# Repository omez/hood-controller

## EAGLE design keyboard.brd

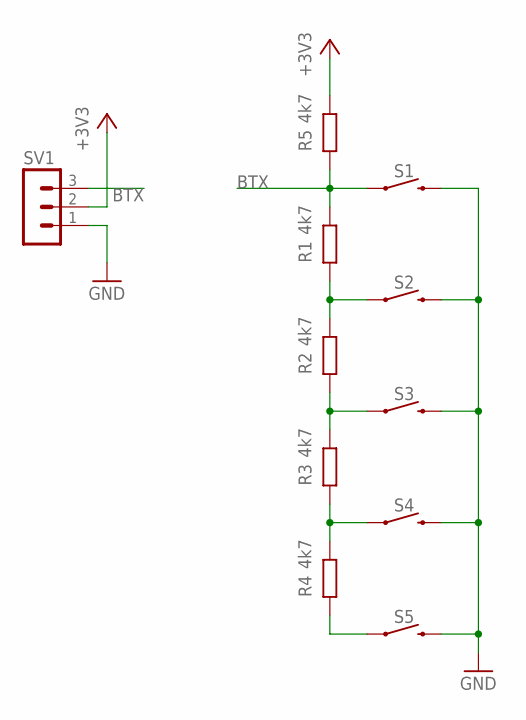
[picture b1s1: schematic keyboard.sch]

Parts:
R1, R2, R3, R4, R5: 4k7; R1206
S1, S2, S3, S4, S5: MOMENTARY-SWITCH-SPST-PTH-6.0MM; TACTILE_SWITCH_PTH_6.0MM
SV1: MA03-1

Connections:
+3V3: R5.2, SV1.2
BTX: R1.2, R5.1, S1.1, SV1.3
GND: S1.3 (2), S2.3 (2), S3.3 (2), S4.3 (2), S5.3 (2), SV1.1
unnamed: R3.1, R4.2, S4.1
unnamed: R4.1, S5.1
unnamed: R2.1, R3.2, S3.1
unnamed: R1.1, R2.2, S2.1

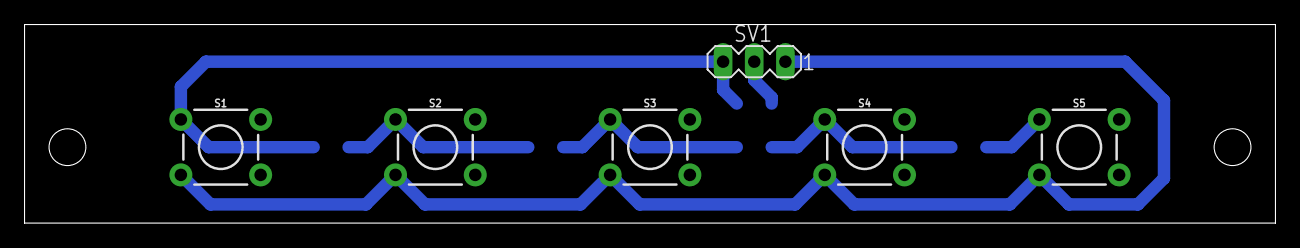
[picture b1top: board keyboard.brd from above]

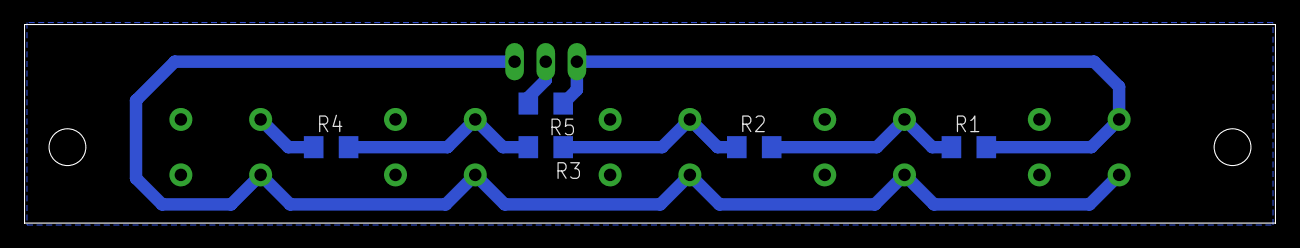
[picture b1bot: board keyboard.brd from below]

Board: 2 copper layers, 102.0 x 16.2 mm, 11 parts (5 on the bottom side), 7 nets.

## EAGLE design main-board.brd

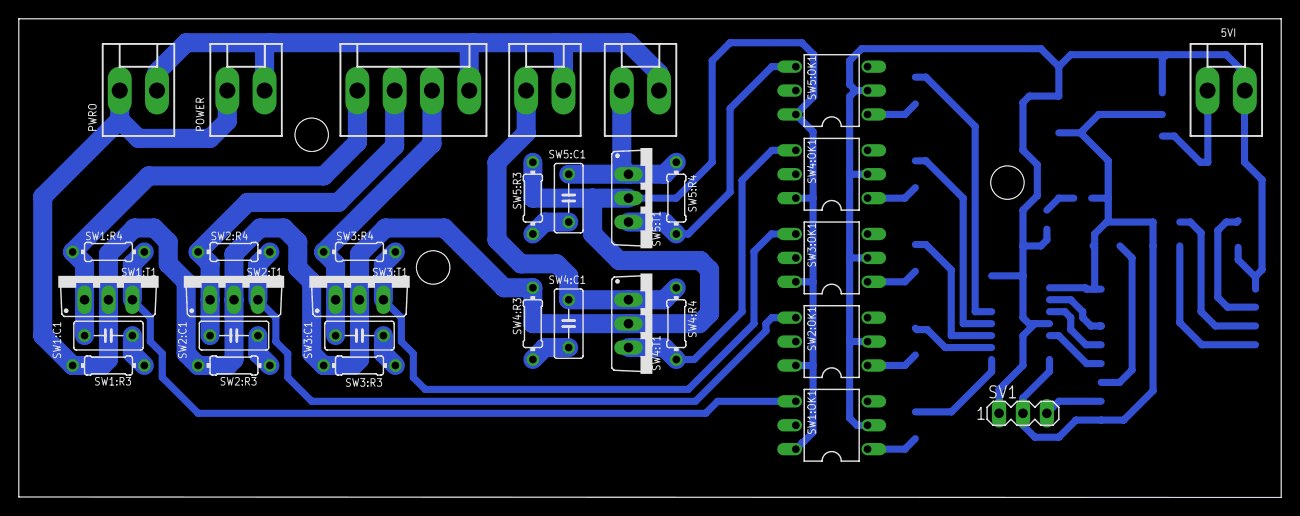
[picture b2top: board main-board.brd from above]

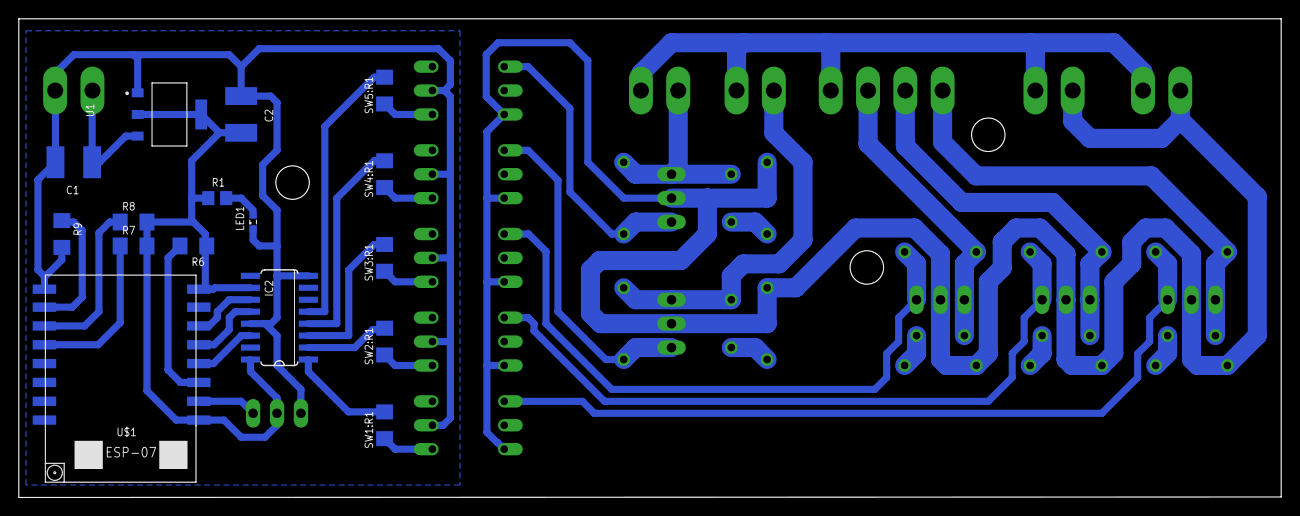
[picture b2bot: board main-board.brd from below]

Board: 2 copper layers, 134.1 x 50.9 mm, 48 parts (16 on the bottom side), 39 nets.

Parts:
5VI: KK-156-2
C1, C2: C4532
IC2: 74HC595D; SO16
LAMP1, LAMP2: KK-156-2
LED1: SML0603
MOTOR: KK-156-4
POWER: KK-156-2
PWRO: KK-156-2
R1: 210; R0805
R6, R7, R8, R9: 4k7; R1206
SV1: MA03-1
SW1:C1, SW2:C1, SW3:C1, SW4:C1, SW5:C1: C050-030X075
SW1:OK1, SW2:OK1, SW3:OK1, SW4:OK1, SW5:OK1: MOC3033M; DIL06
SW1:R1, SW2:R1, SW3:R1, SW4:R1, SW5:R1: 100; R1206
SW1:R3, SW2:R3, SW3:R3, SW4:R3, SW5:R3: 39; 0204/7
SW1:R4, SW2:R4, SW3:R4, SW4:R4, SW5:R4: 360; 0204/7
SW1:T1, SW2:T1, SW3:T1, SW4:T1, SW5:T1: BT138-V; TO220BV
U1: LD1117S33TR; SOT-223
U$1: ESP07-16PIN

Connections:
+3V3: C2.1, IC2.10, IC2.16, R1.1, R6.1, R7.2, R8.2, SV1.2, U1.2, U1.4, U$1.REST, U$1.VCC
+5V: 5VI.1, C1.1, U1.3
AC+: POWER.1, PWRO.1, SW1:OK1.6, SW1:R3.2, SW1:T1.T2, SW2:OK1.6, SW2:R3.2, SW2:T1.T2, SW3:OK1.6, SW3:R3.2, SW3:T1.T2, SW4:OK1.6, SW4:R3.2, SW4:T1.T2, SW5:OK1.6, SW5:R3.2, SW5:T1.T2
AC-: LAMP1.2, LAMP2.2, MOTOR.4, POWER.2, PWRO.2
BTX: SV1.3, U$1.ADC
CDT: IC2.14, U$1.GPIO16
CLT: IC2.12, U$1.GPIO14
CSCK: IC2.11, U$1.GPIO12
GND: 5VI.2, C1.2, C2.2, IC2.8, IC2.13, LED1.C, R9.2, SV1.1, SW1:OK1.2, SW2:OK1.2, SW3:OK1.2, SW4:OK1.2, SW5:OK1.2, U1.1, U$1.GND
LAMP1: LAMP1.1, SW5:C1.2, SW5:R4.1, SW5:T1.T1
LAMP2: LAMP2.1, SW4:C1.2, SW4:R4.1, SW4:T1.T1
M1: MOTOR.1, SW1:C1.2, SW1:R4.1, SW1:T1.T1
M2: MOTOR.2, SW2:C1.2, SW2:R4.1, SW2:T1.T1
M3: MOTOR.3, SW3:C1.2, SW3:R4.1, SW3:T1.T1
unnamed: IC2.2, SW2:R1.1
unnamed: LED1.A, R1.2
unnamed: IC2.4, SW4:R1.1
unnamed: IC2.1, SW1:R1.1
unnamed: IC2.3, SW3:R1.1
unnamed: IC2.5, SW5:R1.1
unnamed: R6.2, U$1.CH_PD
unnamed: R7.1, U$1.GPIO0
unnamed: R8.1, U$1.GPIO2
unnamed: R9.1, U$1.GPIO15
SW1:ACS: SW1:OK1.4, SW1:R4.2, SW1:T1.G
SW1:N$1: SW1:OK1.1, SW1:R1.2
SW1:N$8: SW1:C1.1, SW1:R3.1
SW2:ACS: SW2:OK1.4, SW2:R4.2, SW2:T1.G
SW2:N$1: SW2:OK1.1, SW2:R1.2
SW2:N$8: SW2:C1.1, SW2:R3.1
SW3:ACS: SW3:OK1.4, SW3:R4.2, SW3:T1.G
SW3:N$1: SW3:OK1.1, SW3:R1.2
SW3:N$8: SW3:C1.1, SW3:R3.1
SW4:ACS: SW4:OK1.4, SW4:R4.2, SW4:T1.G
SW4:N$1: SW4:OK1.1, SW4:R1.2
SW4:N$8: SW4:C1.1, SW4:R3.1
SW5:ACS: SW5:OK1.4, SW5:R4.2, SW5:T1.G
SW5:N$1: SW5:OK1.1, SW5:R1.2
SW5:N$8: SW5:C1.1, SW5:R3.1

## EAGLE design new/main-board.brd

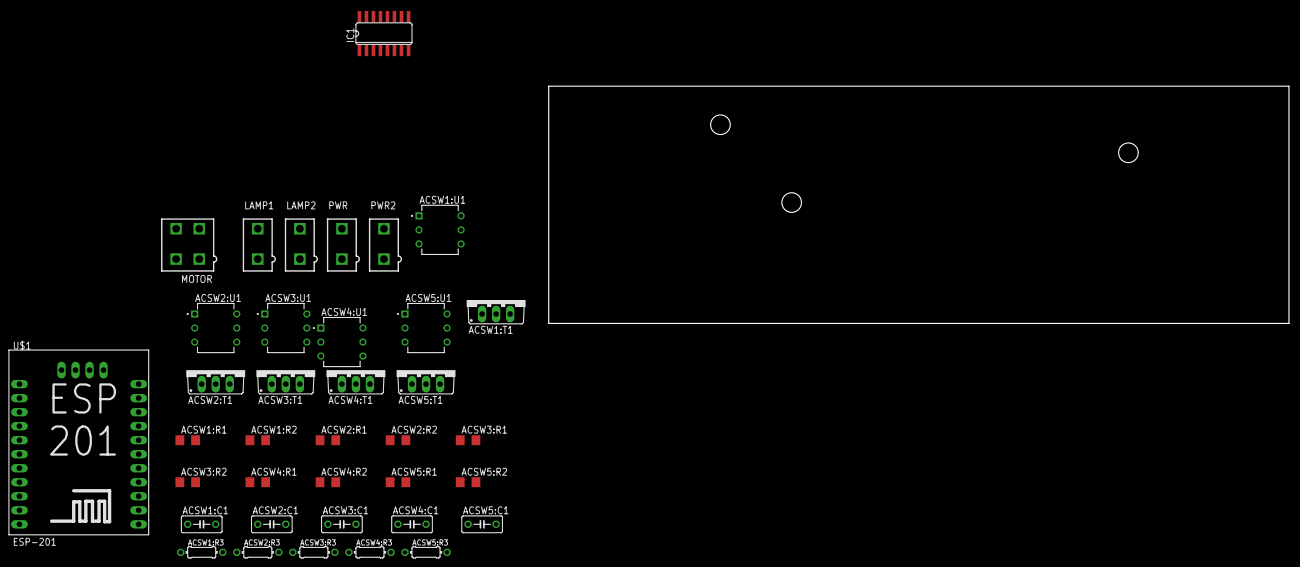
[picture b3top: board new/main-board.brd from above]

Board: 2 copper layers, 134.1 x 43.0 mm, 37 parts (0 on the bottom side), 38 nets, no tracks yet.

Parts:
ACSW1:C1, ACSW2:C1, ACSW3:C1, ACSW4:C1, ACSW5:C1: C050-030X075
ACSW1:R1, ACSW2:R1, ACSW3:R1, ACSW4:R1, ACSW5:R1: 100; R1206
ACSW1:R2, ACSW2:R2, ACSW3:R2, ACSW4:R2, ACSW5:R2: 360; R1206
ACSW1:R3, ACSW2:R3, ACSW3:R3, ACSW4:R3, ACSW5:R3: 0204/7
ACSW1:T1, ACSW2:T1, ACSW3:T1, ACSW4:T1, ACSW5:T1: BT138-V; TO220BV
ACSW1:U1, ACSW2:U1, ACSW3:U1, ACSW4:U1, ACSW5:U1: MOC3012M
IC1: 74LS595D; SO16
LAMP1, LAMP2: 5566-2
MOTOR: 5566-4
PWR, PWR2: 5566-2
U$1: ESP-201

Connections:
ACSW1:AC+: ACSW1:R3.2, ACSW1:T1.T2, ACSW1:U1.6
ACSW1:AC-: ACSW1:C1.2, ACSW1:T1.T1
ACSW1:N$1: ACSW1:R1.2, ACSW1:U1.1
ACSW1:N$2: ACSW1:R2.1, ACSW1:U1.4
ACSW1:N$5: ACSW1:R2.2, ACSW1:T1.G
ACSW1:N$8: ACSW1:C1.1, ACSW1:R3.1
ACSW2:AC+: ACSW2:R3.2, ACSW2:T1.T2, ACSW2:U1.6
ACSW2:AC-: ACSW2:C1.2, ACSW2:T1.T1
ACSW2:N$1: ACSW2:R1.2, ACSW2:U1.1
ACSW2:N$2: ACSW2:R2.1, ACSW2:U1.4
ACSW2:N$5: ACSW2:R2.2, ACSW2:T1.G
ACSW2:N$8: ACSW2:C1.1, ACSW2:R3.1
ACSW3:AC+: ACSW3:R3.2, ACSW3:T1.T2, ACSW3:U1.6
ACSW3:AC-: ACSW3:C1.2, ACSW3:T1.T1
ACSW3:N$1: ACSW3:R1.2, ACSW3:U1.1
ACSW3:N$2: ACSW3:R2.1, ACSW3:U1.4
ACSW3:N$5: ACSW3:R2.2, ACSW3:T1.G
ACSW3:N$8: ACSW3:C1.1, ACSW3:R3.1
ACSW4:AC+: ACSW4:R3.2, ACSW4:T1.T2, ACSW4:U1.6
ACSW4:AC-: ACSW4:C1.2, ACSW4:T1.T1
ACSW4:N$1: ACSW4:R1.2, ACSW4:U1.1
ACSW4:N$2: ACSW4:R2.1, ACSW4:U1.4
ACSW4:N$5: ACSW4:R2.2, ACSW4:T1.G
ACSW4:N$8: ACSW4:C1.1, ACSW4:R3.1
ACSW5:AC+: ACSW5:R3.2, ACSW5:T1.T2, ACSW5:U1.6
ACSW5:AC-: ACSW5:C1.2, ACSW5:T1.T1
ACSW5:N$1: ACSW5:R1.2, ACSW5:U1.1
ACSW5:N$2: ACSW5:R2.1, ACSW5:U1.4
ACSW5:N$5: ACSW5:R2.2, ACSW5:T1.G
ACSW5:N$8: ACSW5:C1.1, ACSW5:R3.1
GND: ACSW2:U1.2, ACSW3:U1.2, ACSW4:U1.2, ACSW5:U1.2, IC1.8, IC1.13
unnamed: ACSW1:R1.1, IC1.15
unnamed: ACSW2:R1.1, IC1.1
unnamed: ACSW3:R1.1, IC1.2
unnamed: ACSW4:R1.1, IC1.3
unnamed: ACSW5:R1.1, IC1.4
PWR+: PWR.2, PWR2.2
PWR-: LAMP1.1, LAMP2.1, MOTOR.1, PWR.1, PWR2.1

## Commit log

2021-02-21 init
2021-02-21 added
2021-02-21 add floder new, with david project

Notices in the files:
parts and their libraries:
SparkFun-Switches: Licensing: Creative Commons ShareAlike 4.0 International - https://creativecommons.org/licenses/by-sa/4.0
